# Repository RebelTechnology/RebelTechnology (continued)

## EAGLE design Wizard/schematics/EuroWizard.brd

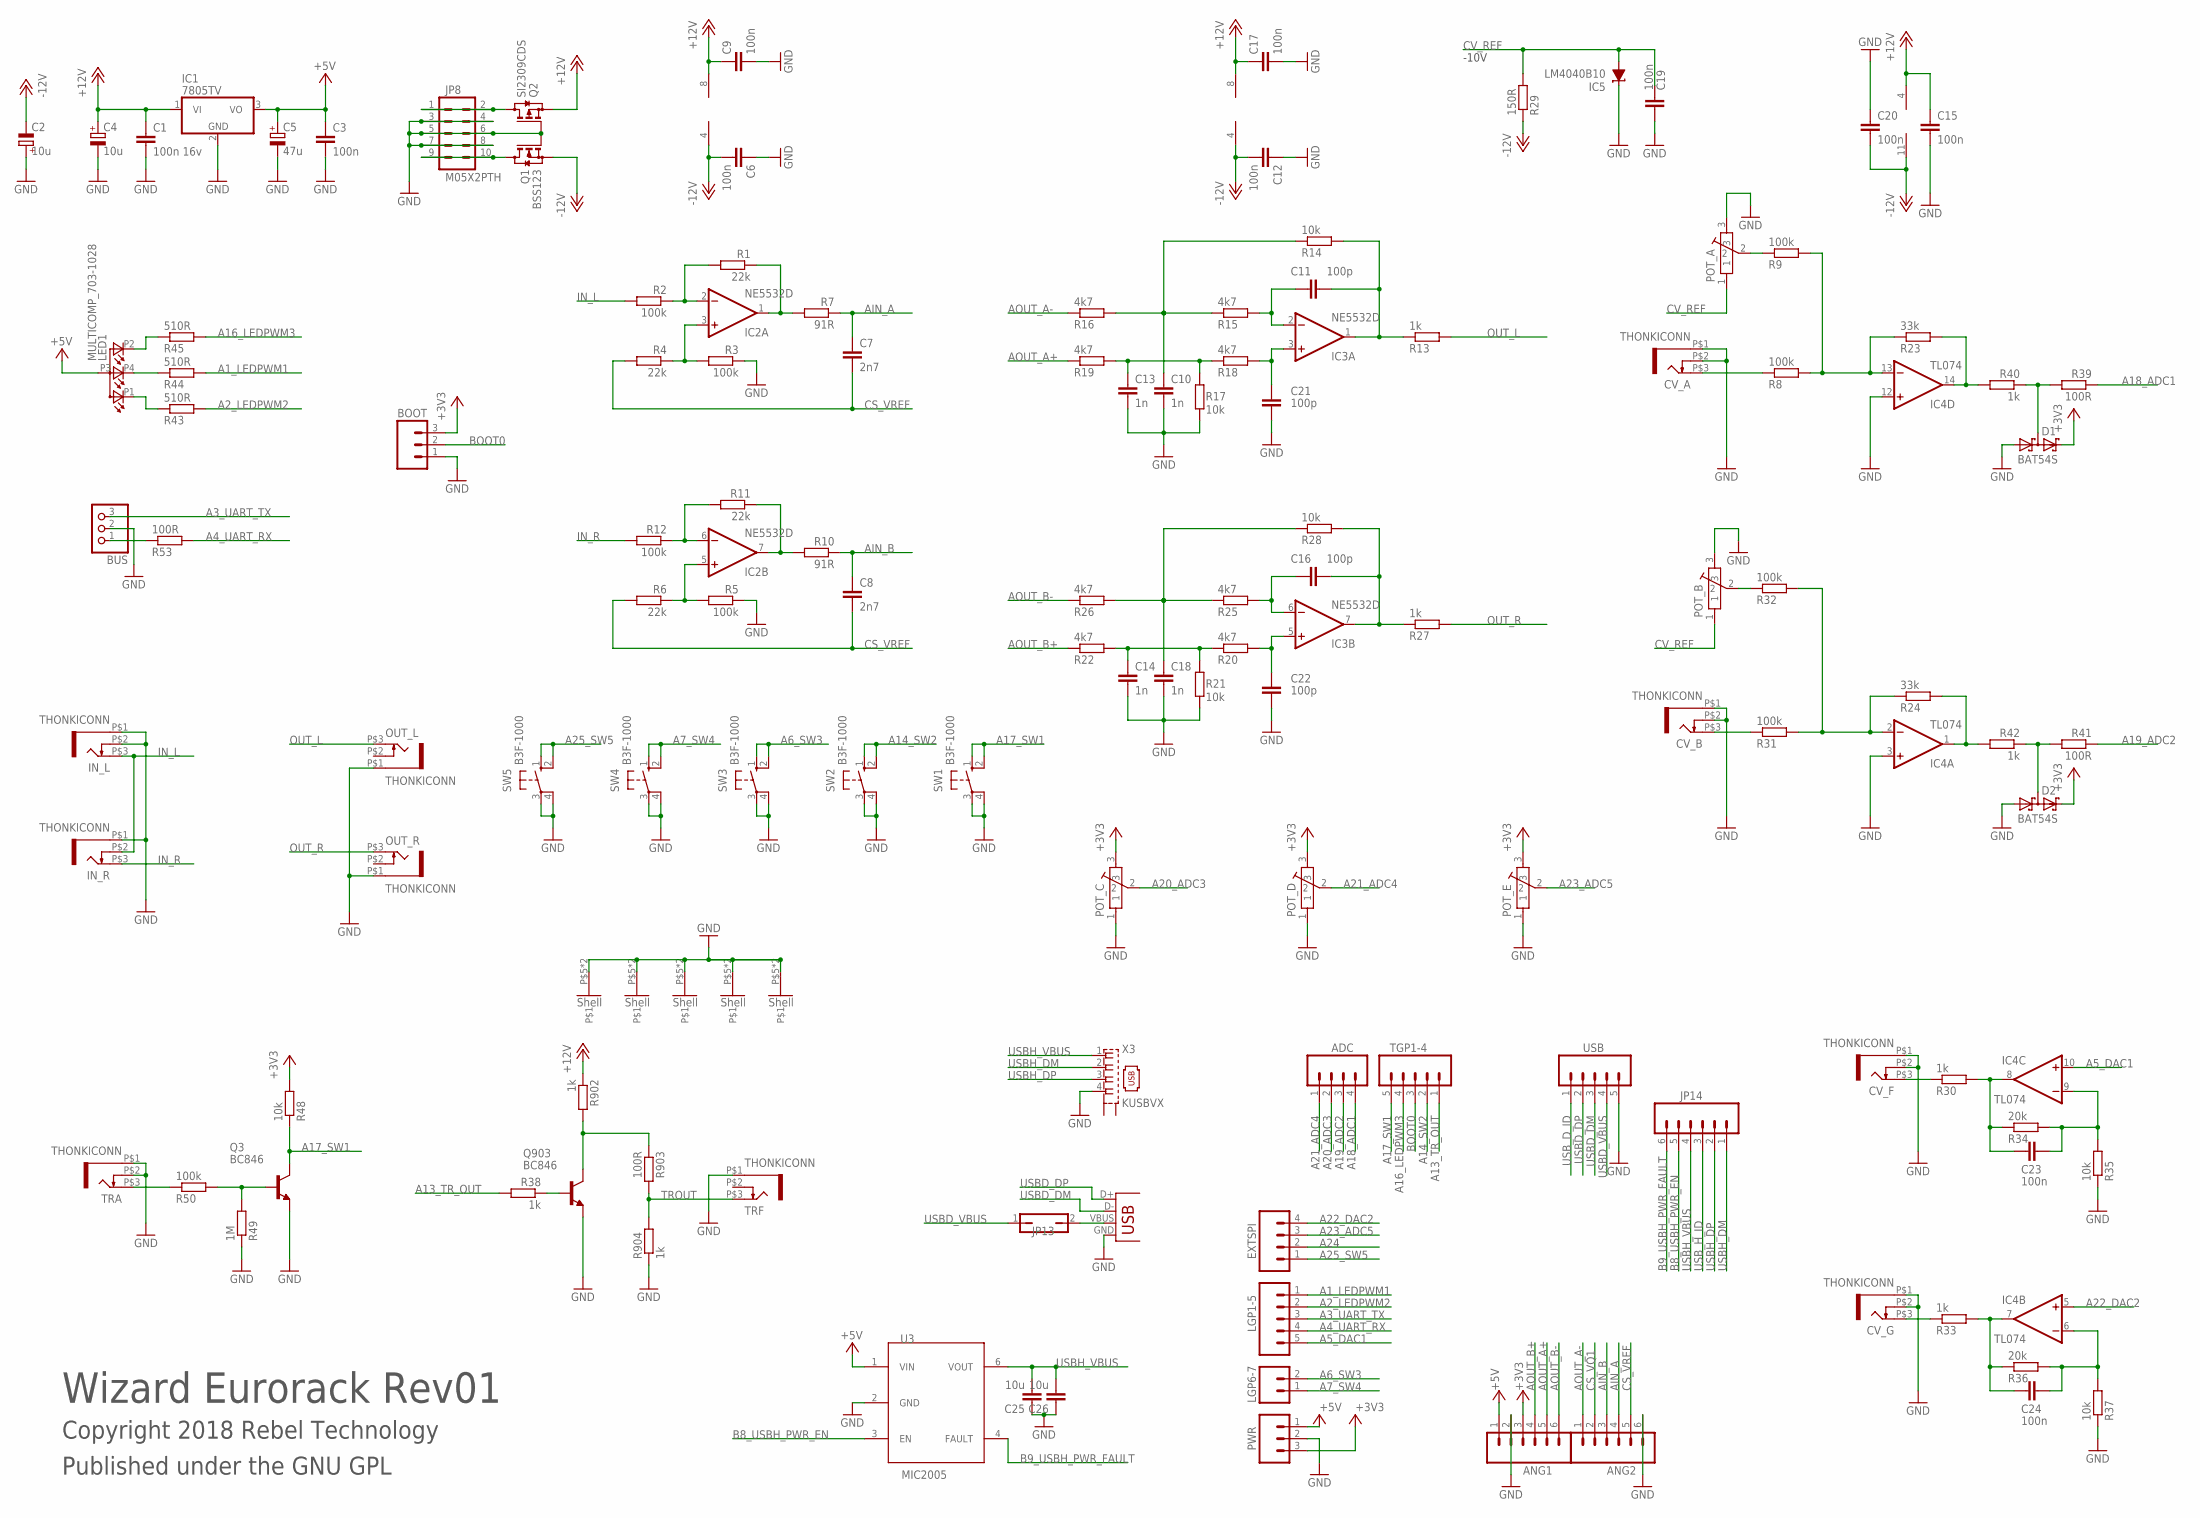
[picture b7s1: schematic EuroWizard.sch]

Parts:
ADC: M04PTH; 1X04
ANG1, ANG2: M06SIP; 1X06
BOOT: M03PTH; 1X03
BUS: CON-JST-1X03PH-TH; JST-B3B-PH-KL
C1: 100n 16v; C0603
C2, C4: 10u; UD-4X5,8_NICHICON
C3, C6, C9, C12, C15, C17, C19, C20, C23, C24: 100n; C0603
C5: 47u; UD-4X5,8_NICHICON
C7, C8: 2n7; C0603
C10, C13, C14, C18: 1n; C0603
C11, C16, C21, C22: 100p; C0603
C25, C26: 10u; C0603
CV_A: THONKICONN
CV_B: THONKICONN
CV_F: THONKICONN
CV_G: THONKICONN
D1, D2: BAT54S; SOT23
EXTSPI: M04PTH; 1X04
IC1: 7805TV; TO220V
IC2, IC3: NE5532D; SO08
IC4: TL074; SO14
IC5: LM4040B10; DBZ_R-PDSO-G3
IN_L: THONKICONN
IN_R: THONKICONN
JP8: M05X2PTH; AVR_ICSP
JP13: JP1Q; JP1
JP14: M06SIP; 1X06
LED1: MULTICOMP_703-1028; RGB-LED-703-1028
LGP1-5: M05PTH; 1X05
LGP6-7: M02PTH; 1X02
OUT_L: THONKICONN
OUT_R: THONKICONN
POT_A: POT-ALPS-RK09L1140
POT_B: POT-ALPS-RK09L1140
POT_C: POT-ALPS-RK09L1140
POT_D: POT-ALPS-RK09L1140
POT_E: POT-ALPS-RK09L1140
PWR: M03PTH; 1X03
Q1: BSS123; SOT23
Q2: SI2309CDS; SOT23
Q3, Q903: BC846; SOT23
R1, R4, R6, R11: 22k; 0603
R2, R3, R5, R8, R9, R12, R31, R32, R50: 100k; 0603
R7, R10: 91R; 0603
R13, R27, R30, R33, R38, R40, R42, R902, R904: 1k; 0603
R14, R17, R21, R28, R35, R37, R48: 10k; 0603
R15, R16, R18, R19, R20, R22, R25, R26: 4k7; 0603
R23, R24: 33k; 0603
R29: 150R; 0603
R34, R36: 20k; 0603
R39, R41, R53, R903: 100R; 0603
R43, R44, R45: 510R; 0603
R49: 1M; 0603
SW1, SW2, SW3, SW4, SW5: B3F-1000; B3F-10XX
TGP1-4: M05PTH; 1X05
TRA: THONKICONN
TRF: THONKICONN
U3: MIC2005; SOT23-6
USB: M05PTH; 1X05
X3: KUSBVX
X5: USBPTH-VERTICAL; USB-B-PTH-VERTICAL

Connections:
+3V3: ANG1.3, BOOT.3, D1.2 (C2), D2.2 (C2), POT_C.3, POT_D.3, POT_E.3, PWR.3, R48.2
+5V: ANG1.1, C3.1, C5.+, IC1.3 (VO), LED1.P3 (A), PWR.1, U3.1 (VIN)
+12V: C1.1, C4.+, C9.1, C15.1, C17.1, IC1.1 (VI), IC2.8 (V+), IC3.8 (V+), IC4.4 (V+), Q2.2 (S), R902.1
-12V: C2.-, C6.2, C12.2, C20.2, IC2.4 (V-), IC3.4 (V-), IC4.11 (V-), Q1.2 (S), R29.1
A1_LEDPWM1: LGP1-5.1, R44.2
A2_LEDPWM2: LGP1-5.2, R43.2
A3_UART_TX: BUS.3, LGP1-5.3
A4_UART_RX: LGP1-5.4, R53.2
A5_DAC1: IC4.10 (+IN), LGP1-5.5
A6_SW3: LGP6-7.2, SW3.1 (S), SW3.2 (S1)
A7_SW4: LGP6-7.1, SW4.1 (S), SW4.2 (S1)
A13_TR_OUT: R38.2, TGP1-4.1
A14_SW2: SW2.1 (S), SW2.2 (S1), TGP1-4.2
A16_LEDPWM3: R45.2, TGP1-4.4
A17_SW1: Q3.3 (C), R48.1, SW1.1 (S), SW1.2 (S1), TGP1-4.5
A18_ADC1: ADC.4, R39.1
A19_ADC2: ADC.3, R41.1
A20_ADC3: ADC.2, POT_C.2
A21_ADC4: ADC.1, POT_D.2
A22_DAC2: EXTSPI.4, IC4.5 (+IN)
A23_ADC5: EXTSPI.3, POT_E.2
A24: EXTSPI.2
A25_SW5: EXTSPI.1, SW5.1 (S), SW5.2 (S1)
AIN_A: ANG2.4, C7.1, R7.1
AIN_B: ANG2.3, C8.1, R10.1
AOUT_A+: ANG1.5, R19.1
AOUT_A-: ANG2.1, R16.1
AOUT_B+: ANG1.4, R22.1
AOUT_B-: ANG1.6, R26.1
B8_USBH_PWR_EN: JP14.5, U3.3 (EN)
B9_USBH_PWR_FAULT: JP14.6, U3.4 (FAULT)
BOOT0: BOOT.2, TGP1-4.3
CS_VQ1: ANG2.2
CS_VREF: ANG2.5, C7.2, C8.2, R4.2, R6.2
CV_REF: C19.1, IC5.2 (A), POT_A.1, POT_B.1, R29.2
EXT_UART_RX: BUS.1, R53.1
GND: ANG1.2, ANG2.6, BOOT.1, BUS.2, C1.2, C2.+, C3.2, C4.-, C5.-, C6.1, C9.2, C10.2, C12.1, C13.2, C14.2, C15.2, C17.2, C18.2, C19.2, C20.1, C21.2, C22.2, C25.1, C26.1, CV_A.P$1 (5), CV_A.P$2 (4), CV_B.P$1 (5), CV_B.P$2 (4), CV_F.P$1 (5), CV_F.P$2 (4), CV_G.P$1 (5), CV_G.P$2 (4), D1.1 (A1), D2.1 (A1), IC1.2 (GND), IC4.3 (+IN), IC4.12 (+IN), IC5.1 (C), IN_L.P$1 (5), IN_L.P$2 (4), IN_R.P$1 (5), JP8.3, JP8.4, JP8.5, JP8.6, JP8.7, JP8.8, OUT_L.P$1 (5), OUT_R.P$1 (5), POT_A.3, POT_A.P$5, POT_A.P$6, POT_B.3, POT_B.P$5, POT_B.P$6, POT_C.1, POT_C.P$5, POT_C.P$6, POT_D.1, POT_D.P$5, POT_D.P$6, POT_E.1, POT_E.P$5, POT_E.P$6, PWR.2, Q1.1 (G), Q2.1 (G), Q3.2 (E), Q903.2 (E), R3.1, R5.1, R17.1, R21.1, R35.1, R37.1, R49.1, R904.1, SW1.3, SW1.4 (P1), SW2.3, SW2.4 (P1), SW3.3, SW3.4 (P1), SW4.3, SW4.4 (P1), SW5.3, SW5.4 (P1), TRA.P$1 (5), TRA.P$2 (4), TRF.P$1 (5), U3.2 (GND), USB.5, X3.4, X5.GND
IN_L: IN_L.P$3 (3), IN_R.P$2 (4), R2.2
IN_R: IN_R.P$3 (3), R12.2
unnamed: IC2.1 (OUT), R1.1, R7.2
unnamed: IC2.3 (+IN), R3.2, R4.1
unnamed: CV_A.P$3 (3), R8.1
unnamed: IC2.5 (+IN), R5.2, R6.1
unnamed: IC2.6 (-IN), R11.2, R12.1
unnamed: CV_F.P$3 (3), R30.1
unnamed: C11.1, IC3.2 (-IN), R15.2
unnamed: JP8.9, JP8.10, Q1.3 (D)
unnamed: IC2.2 (-IN), R1.2, R2.1
unnamed: IC2.7 (OUT), R10.2, R11.1
unnamed: C21.1, IC3.3 (+IN), R18.2
unnamed: JP8.1, JP8.2, Q2.3 (D)
unnamed: IC4.13 (-IN), R8.2, R9.2, R23.1
unnamed: POT_A.2, R9.1
unnamed: C13.1, R17.2, R18.1, R19.2
unnamed: D1.3 (C1A2), R39.2, R40.1
unnamed: IC4.14 (OUT), R23.2, R40.2
unnamed: C16.2, IC3.7 (OUT), R27.1, R28.2
unnamed: CV_B.P$3 (3), R31.1
unnamed: IC4.2 (-IN), R24.1, R31.2, R32.2
unnamed: POT_B.2, R32.1
unnamed: IC4.1 (OUT), R24.2, R42.2
unnamed: D2.3 (C1A2), R41.2, R42.1
unnamed: C18.1, R25.1, R26.2, R28.1
unnamed: C23.2, IC4.8 (OUT), R30.2, R34.1
unnamed: C16.1, IC3.6 (-IN), R25.2
unnamed: JP13.2, X5.VBUS
unnamed: CV_G.P$3 (3), R33.1
unnamed: C23.1, IC4.9 (-IN), R34.2, R35.2
unnamed: C22.1, IC3.5 (+IN), R20.2
unnamed: C24.2, IC4.7 (OUT), R33.2, R36.1
unnamed: C14.1, R20.1, R21.2, R22.2
unnamed: C24.1, IC4.6 (-IN), R36.2, R37.2
unnamed: Q3.1 (B), R49.2, R50.2
unnamed: C11.2, IC3.1 (OUT), R13.1, R14.2
unnamed: LED1.P1 (CRED), R43.1
unnamed: C10.1, R14.1, R15.1, R16.2
unnamed: LED1.P2 (CGREEN), R45.1
unnamed: LED1.P4 (CBLUE), R44.1
unnamed: R50.1, TRA.P$3 (3)
unnamed: Q903.1 (B), R38.1
unnamed: Q903.3 (C), R902.2, R903.1
OUT_L: OUT_L.P$3 (3), R13.2
OUT_R: OUT_R.P$3 (3), R27.2
TROUT: R903.2, R904.2, TRF.P$3 (3)
USBD_DM: USB.3, X5.D-
USBD_DP: USB.2, X5.D+
USBD_VBUS: JP13.1, USB.4
USBH_DM: JP14.1, X3.2
USBH_DP: JP14.2, X3.3
USBH_VBUS: C25.2, C26.2, JP14.4, U3.6 (VOUT), X3.1
USB_D_ID: USB.1
USB_H_ID: JP14.3

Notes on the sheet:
Wizard Eurorack Rev01
Copyright 2018 Rebel Technology
Published under the GNU GPL
-10V

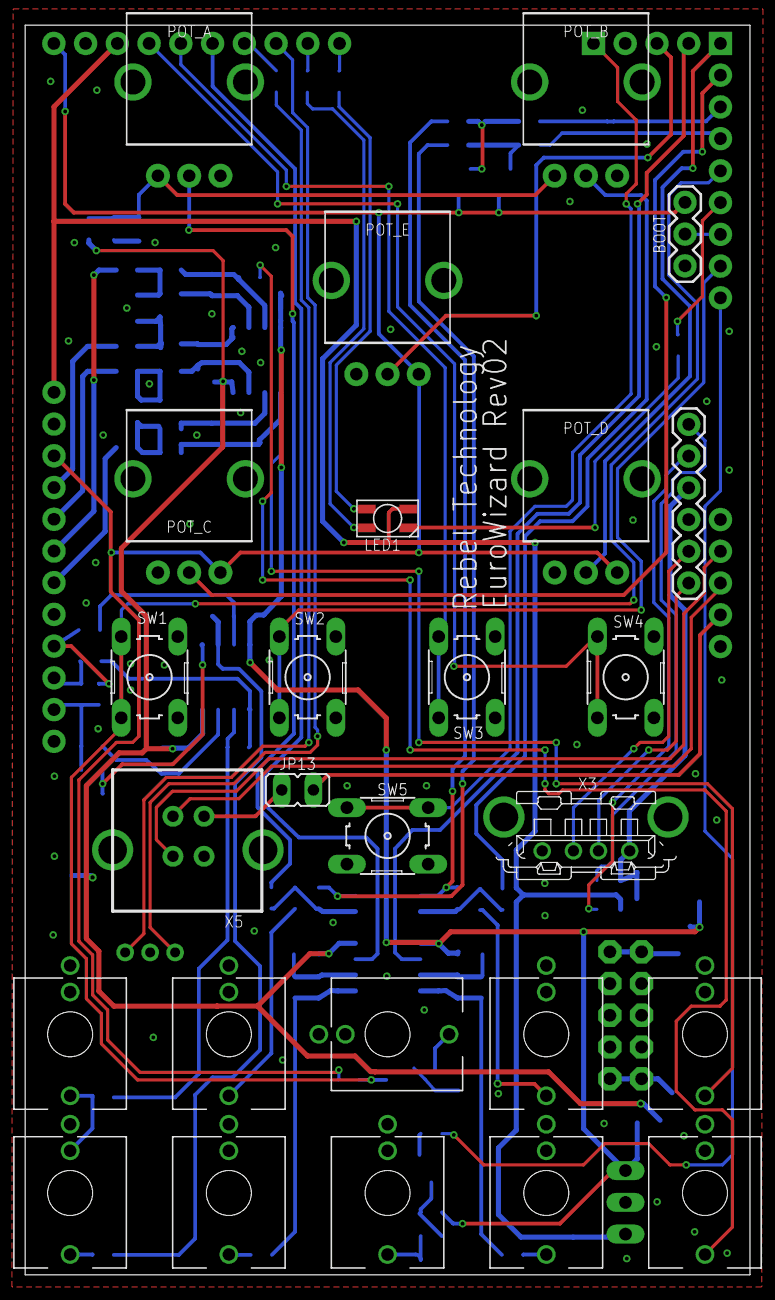
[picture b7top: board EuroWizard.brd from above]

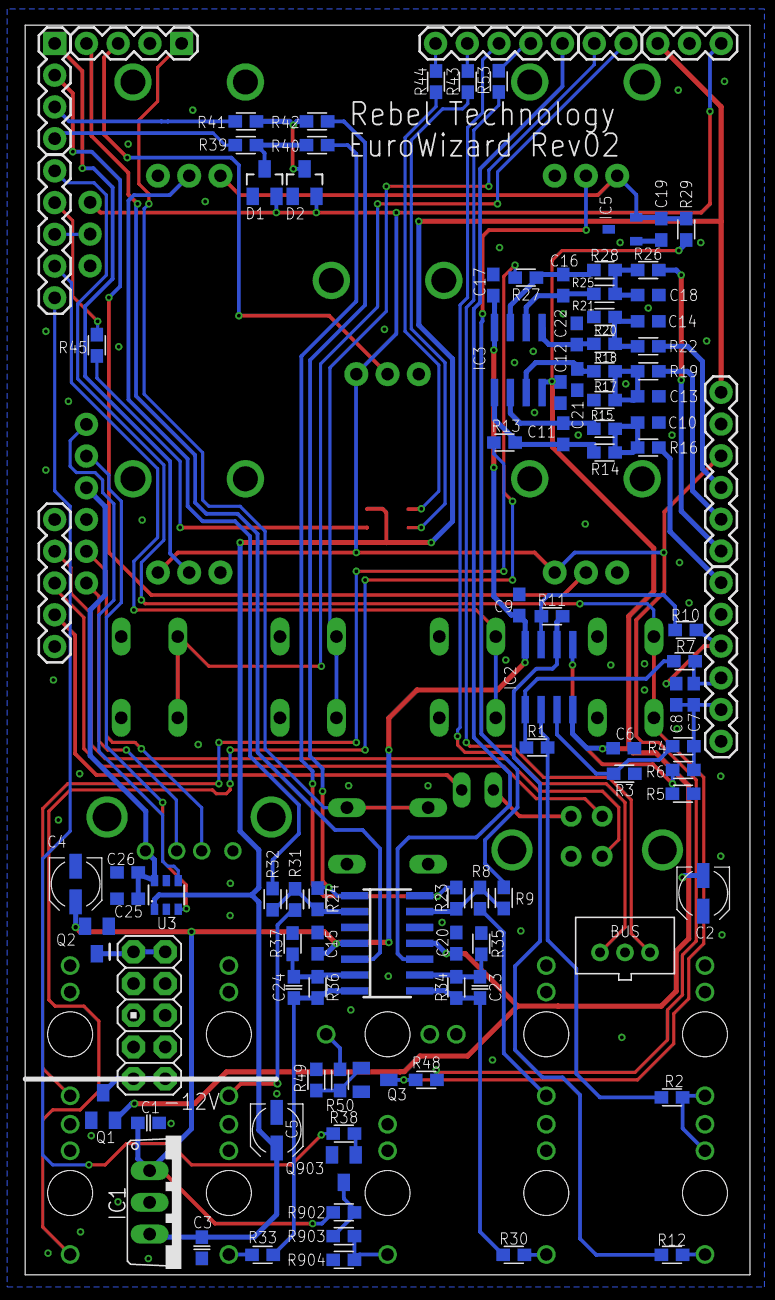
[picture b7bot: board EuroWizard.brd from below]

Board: 2 copper layers, 58.0 x 100.0 mm, 127 parts (101 on the bottom side), 88 nets.
